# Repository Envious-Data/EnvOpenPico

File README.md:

# EnvOpenPico
A RP2040 Based family of MCU boards

### Intentions and Info
The intentions of this project were mainly to learn about MCU design and also to make a rpi pico like device using a RP2040 that has some improvements or changes that you'd find useful, so far Ive changed the type-c port and added a reset button as well as replaced the buck boost IC with a linear regulator which doesnt generate the same switching noise which makes it good for audio.

Ive retained the USB TP pads and also TP6 which is bootsel in their original positions.
a couple of the GPIOs cant retain their original function since Im not using a RT6150B-33GQW so GPIO23 has an optional mosfet for a default on LED instead of controlling the mode for the buck-boost IC.

Ive also got nothing connected on GPIO29 where as the pico has a mosfet to prevent leakage current, im not sure what the use of this GPIO is but if its a wanted feature I can try to add it back.

Update: 09th Aug 2024 - Raspberry pi has released the RP235XA and RP235XB, I have started work on making variants of the main Pico board to fit the RP2350 and RP2354.

### Permissions
You have my permission to fork and learn from this design for your own projects including if you wish to sell those on as a product. 

### Important!!
I have only had the EnvOpenPico made so the other variants like the PicoLipo and the EliteMicro2040 I cant fully confirm if the design works but since its all derived from the main project I should hope it all works as intended.

### Notes
- You should be able to order these and have them entirely assembled by other PCBA suppliers if they have stock of all the parts, ive made sure to label everything in the schematic properly.
- Please ensure you pick a compatible flash chip, you may need to modify the connections to the flash chip, its setup for Winbond W25QxxJVxxx.

### Other
If you want to see pictures of the main PCB you can check out the _photos folder

PCBway kindly sponsored a batch of PCBs which you can see pictures of inside the _photos folder.

http://pcbway.com

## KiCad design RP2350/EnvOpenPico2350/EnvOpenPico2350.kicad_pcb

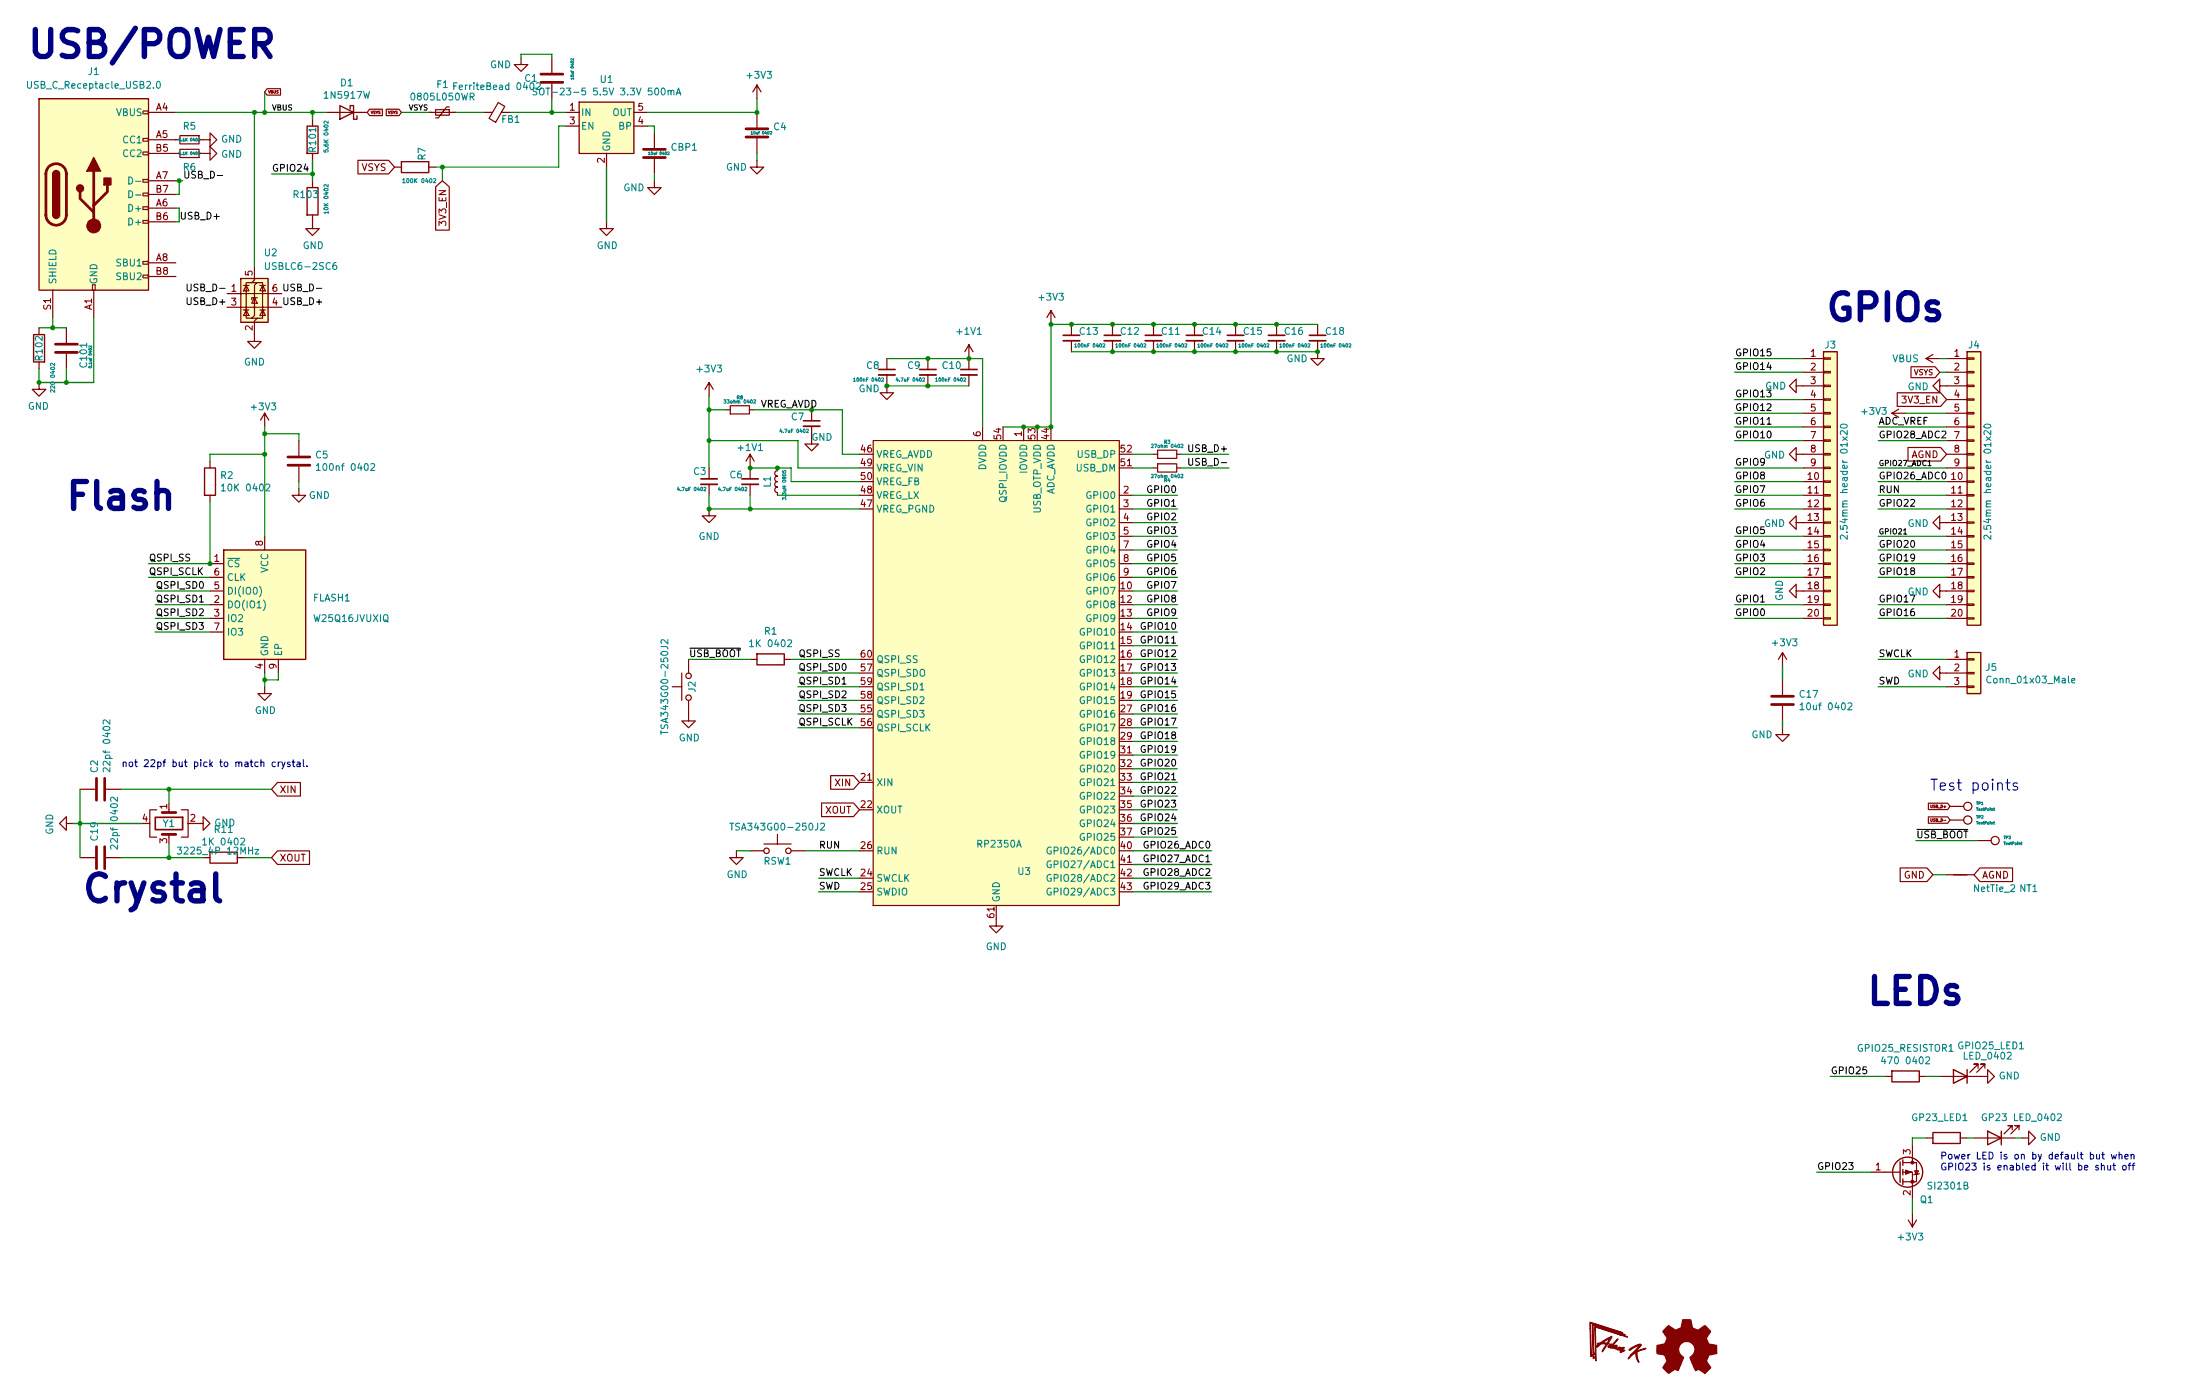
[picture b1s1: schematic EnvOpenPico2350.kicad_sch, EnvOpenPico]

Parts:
C1, C4, C17: 10uf 0402; C_0402_1005Metric
C2, C19: 22pf 0402; C_0402_1005Metric
C3, C6, C7, C9: 4.7uF 0402; C_0402_1005Metric
C5: 100nf 0402; C_0402_1005Metric
C8, C10, C11, C12, C13, C14, C15, C16, C18: 100nF 0402; C_0402_1005Metric
C101: 0.1uf 0402; C_0402_1005Metric
CBP1: 10uf 0402; C_0402_1005Metric
D1: 1N5917W; D_SOD-123
F1: 0805L050WR; Fuse_0805_2012Metric
FB1: FerriteBead 0402; R_0402_1005Metric
FLASH1: W25Q16JVUXIQ; Winbond_USON-8-1EP_3x2mm_P0.5mm_EP0.2x1.6mm
GP23_LED1: GP23 LED_0402; LED_0402_1005Metric
GPIO24_RESISTOR1: 1K 0402; R_0402_1005Metric
GPIO25_LED1: LED_0402; LED_0402_1005Metric
GPIO25_RESISTOR1: 470 0402; R_0402_1005Metric
J1: USB_C_Receptacle_USB2.0; USB_C_Receptacle_HRO_TYPE-C-31-M-12
J2: TSA343G00-250J2; SW_Push_SPST_NO_Alps_SKRK
J3, J4: 2.54mm header 01x20; PinHeader_1x20_P2.54mm_Vertical
J5: Conn_01x03_Male; PinHeader_1x03_P2.54mm_Vertical
L1: 3.3uH 0805; L_0805_2012Metric
NT1: NetTie_2; NetTie-2_SMD_Pad0.5mm
Q1: SI2301B; SOT-23
R1, R11: 1K 0402; R_0402_1005Metric
R2, R103: 10K 0402; R_0402_1005Metric
R3, R4: 27ohm 0402; R_0402_1005Metric
R5, R6: 5.1K 0402; R_0402_1005Metric
R7: 100K 0402; R_0402_1005Metric
R8: 33ohm 0402; R_0402_1005Metric
R101: 5.6K 0402; R_0402_1005Metric
R102: 220 0402; R_0402_1005Metric
RSW1: TSA343G00-250J2; SW_Push_SPST_NO_Alps_SKRK
TP1, TP2, TP3: TestPoint; CustomTestPoint
U1: SOT-23-5 5.5V 3.3V 500mA; SOT-23-5
U2: USBLC6-2SC6; SOT-23-6
U3: RP2350A; QFN-60-1EP_7x7mm_P0.4mm_EP3.4x3.4mm_ThermalVias
Y1: 3225_4P 12MHz; Crystal_SMD_3225-4Pin_3.2x2.5mm

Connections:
3V3_EN: J4.4, R7.1, U1.3 (EN)
+1V1: C6.1, C8.1, C9.1, C10.1, L1.1, U3.6 (DVDD), U3.23 (DVDD), U3.39 (DVDD), U3.50 (VREG_FB)
+3V3: C3.1, C4.1, C5.1, C11.1, C12.1, C13.1, C14.1, C15.1, C16.1, C17.1, C18.1, FLASH1.8 (VCC), J4.5, Q1.2 (S), R2.1, R8.1, U1.5 (OUT), U3.1 (IOVDD), U3.11 (IOVDD), U3.20 (IOVDD), U3.30 (IOVDD), U3.38 (IOVDD), U3.44 (ADC_AVDD), U3.45 (IOVDD), U3.49 (VREG_VIN), U3.53 (USB_OTP_VDD), U3.54 (QSPI_IOVDD)
/ADC_VREF: J4.6
/GPIO0: J3.20, U3.2 (GPIO0)
/GPIO1: J3.19, U3.3 (GPIO1)
/GPIO2: J3.17, U3.4 (GPIO2)
/GPIO3: J3.16, U3.5 (GPIO3)
/GPIO4: J3.15, U3.7 (GPIO4)
/GPIO5: J3.14, U3.8 (GPIO5)
/GPIO6: J3.12, U3.9 (GPIO6)
/GPIO7: J3.11, U3.10 (GPIO7)
/GPIO8: J3.10, U3.12 (GPIO8)
/GPIO9: J3.9, U3.13 (GPIO9)
/GPIO10: J3.7, U3.14 (GPIO10)
/GPIO11: J3.6, U3.15 (GPIO11)
/GPIO12: J3.5, U3.16 (GPIO12)
/GPIO13: J3.4, U3.17 (GPIO13)
/GPIO14: J3.2, U3.18 (GPIO14)
/GPIO15: J3.1, U3.19 (GPIO15)
/GPIO16: J4.20, U3.27 (GPIO16)
/GPIO17: J4.19, U3.28 (GPIO17)
/GPIO18: J4.17, U3.29 (GPIO18)
/GPIO19: J4.16, U3.31 (GPIO19)
/GPIO20: J4.15, U3.32 (GPIO20)
/GPIO21: J4.14, U3.33 (GPIO21)
/GPIO22: J4.12, U3.34 (GPIO22)
/GPIO23: Q1.1 (G), U3.35 (GPIO23)
/GPIO24: R101.2, R103.1, U3.36 (GPIO24)
/GPIO25: GPIO25_RESISTOR1.2, U3.37 (GPIO25)
/GPIO26_ADC0: J4.10, U3.40 (GPIO26/ADC0)
/GPIO27_ADC1: J4.9, U3.41 (GPIO27/ADC1)
/GPIO28_ADC2: J4.7, U3.42 (GPIO28/ADC2)
/GPIO29_ADC3: U3.43 (GPIO29/ADC3)
/QSPI_SCLK: FLASH1.6 (CLK), U3.56 (QSPI_SCLK)
/QSPI_SD0: FLASH1.5 (DI(IO0)), U3.57 (QSPI_SDO)
/QSPI_SD1: FLASH1.2 (DO(IO1)), U3.59 (QSPI_SD1)
/QSPI_SD2: FLASH1.3 (IO2), U3.58 (QSPI_SD2)
/QSPI_SD3: FLASH1.7 (IO3), U3.55 (QSPI_SD3)
/QSPI_SS: FLASH1.1 (~CS), R1.1, R2.2, U3.60 (QSPI_SS)
/RUN: J4.11, RSW1.2, U3.26 (RUN)
/SWCLK: J5.1, U3.24 (SWCLK)
/SWD: J5.3, U3.25 (SWDIO)
/VREG_AVDD: C7.1, R8.2, U3.46 (VREG_AVDD)
/~USB_BOOT: J2.2, R1.2, TP3.1
AGND: J4.8, NT1.2
GND: C1.2, C2.1, C3.2, C4.2, C5.2, C6.2, C7.2, C8.2, C9.2, C10.2, C11.2, C12.2, C13.2, C14.2, C15.2, C16.2, C17.2, C18.2, C19.1, C101.1, CBP1.2, FLASH1.4 (GND), FLASH1.9 (EP), GP23_LED1.1 (K), GPIO25_LED1.1 (K), J1.A1 (GND), J1.A12 (GND), J1.B1 (GND), J1.B12 (GND), J2.1, J3.3, J3.8, J3.13, J3.18, J4.3, J4.13, J4.18, J5.2, NT1.1, R5.1, R6.1, R102.2, R103.2, RSW1.1, U1.2 (GND), U2.2 (GND), U3.47 (VREG_PGND), U3.61 (GND), Y1.2, Y1.4
unnamed: C19.2, R11.2, Y1.3
unnamed: F1.1, FB1.1
unnamed: GP23_LED1.2 (A), GPIO24_RESISTOR1.1
unnamed: GPIO25_LED1.2 (A), GPIO25_RESISTOR1.1
unnamed: J1.A5 (CC1), R5.2
unnamed: J1.B5 (CC2), R6.2
unnamed: C101.2, J1.S1 (SHIELD), R102.1
unnamed: GPIO24_RESISTOR1.2, Q1.3 (D)
unnamed: CBP1.1, U1.4 (BP)
unnamed: C1.1, FB1.2, U1.1 (IN)
unnamed: R4.1, U3.51 (USB_DM)
unnamed: R3.1, U3.52 (USB_DP)
unnamed: L1.2, U3.48 (VREG_LX)
USB_D+: J1.A6 (D+), J1.B6 (D+), R3.2, TP1.1, U2.3 (I/O2), U2.4 (I/O2)
USB_D-: J1.A7 (D-), J1.B7 (D-), R4.2, TP2.1, U2.1 (I/O1), U2.6 (I/O1)
VBUS: D1.2 (A), J1.A4 (VBUS), J1.A9 (VBUS), J1.B4 (VBUS), J1.B9 (VBUS), J4.1, R101.1, U2.5 (VBUS)
VSYS: D1.1 (K), F1.2, J4.2, R7.2
XIN: C2.2, U3.21 (XIN), Y1.1
XOUT: R11.1, U3.22 (XOUT)

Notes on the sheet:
Power LED is on by default but when GPIO23 is enabled it will be shut off
GPIOs
USB/POWER
Flash
not 22pf but pick to match crystal.
Test points
LEDs
Crystal

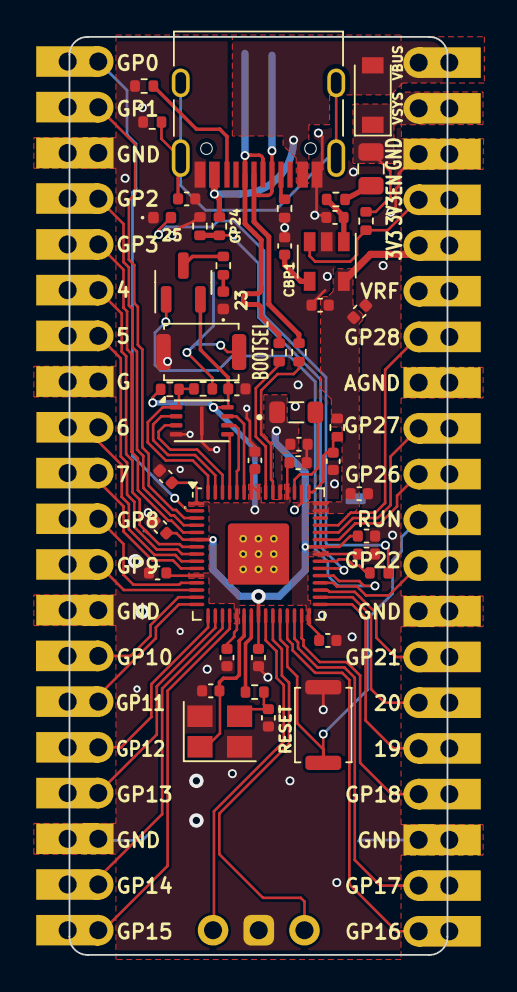
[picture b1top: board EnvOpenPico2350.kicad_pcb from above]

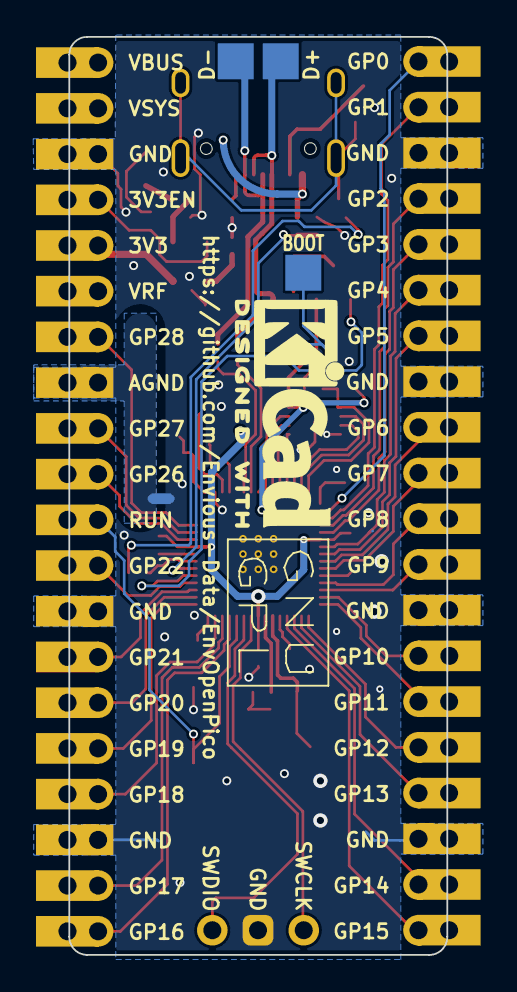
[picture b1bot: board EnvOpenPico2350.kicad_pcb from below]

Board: 2 copper layers, 21.0 x 51.0 mm, 56 parts (6 on the bottom side), 64 nets.

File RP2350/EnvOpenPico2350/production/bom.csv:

Designator,Footprint,Quantity,Value,LCSC Part #
"C1, C17, C4, CBP1",0402,4,10uf 0402, 
"C10, C11, C12, C13, C14, C15, C16, C18, C8",0402,9,100nF 0402,
C101,0402,1,0.1uf 0402, 
"C19, C2",0402,2,22pf 0402, 
"C3, C6, C7, C9",0402,4,4.7uF 0402,
C5,0402,1,100nf 0402, 
D1,D_SOD-123,1,1N5917W, 
F1,0805,1,0805L050WR,
FB1,0402,1,FerriteBead 0402,
FLASH1,Winbond_USON-8-1EP_3x2mm_P0.5mm_EP0.2x1.6mm,1,W25Q16JVUXIQ,
GP23_LED1,0402,1,GP23 LED_0402, 
"GPIO24_RESISTOR1, R1, R11",0402,3,1K 0402, 
GPIO25_LED1,0402,1,LED_0402, 
GPIO25_RESISTOR1,0402,1,470 0402, 
J1,USB_C_Receptacle_HRO_TYPE-C-31-M-12,1,USB_C_Receptacle_USB2.0,
J2,SW_Push_SPST_NO_Alps_SKRK,1,TSA343G00-250J2, 
"J3, J4",PinHeader_1x20_P2.54mm_Vertical,2,2.54mm header 01x20, 
J5,PinHeader_1x03_P2.54mm_Vertical,1,Conn_01x03_Male, 
L1,0805,1,3.3uH 0805,
NT1,NetTie-2_SMD_Pad0.5mm,1,NetTie_2,
Q1,SOT-23,1,SI2301B,
R101,0402,1,5.6K 0402, 
R102,0402,1,220 0402, 
R103,0402,1,10K 0402, 
R2,0402,1,10K 0402,  
"R3, R4",0402,2,27ohm 0402,
"R5, R6",0402,2,5.1K 0402, 
R7,0402,1,100K 0402, 
R8,0402,1,33ohm 0402,
RSW1,SW_Push_SPST_NO_Alps_SKRK,1,TSA343G00-250J2,
"TP1, TP2, TP3",CustomTestPoint,3,TestPoint, 
U1,SOT-23-5,1,SOT-23-5 5.5V 3.3V 500mA, 
U3,QFN-60-1EP_7x7mm_P0.4mm_EP3.4x3.4mm_ThermalVias,1,RP2350A,
Y1,Crystal_SMD_3225-4Pin_3.2x2.5mm,1,3225_4P 12MHz,

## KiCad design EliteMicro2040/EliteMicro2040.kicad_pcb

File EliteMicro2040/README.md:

# EnvOpenPico
A Raspberry Pi RP2040 based board in the shape of an Elite-C.

### Info
This board is about 2.5mm shorter than an Elite-C and uses a mid-mount USB C port.

### some notes
I dont update the readme very often so some info here may end up outdated at some point.

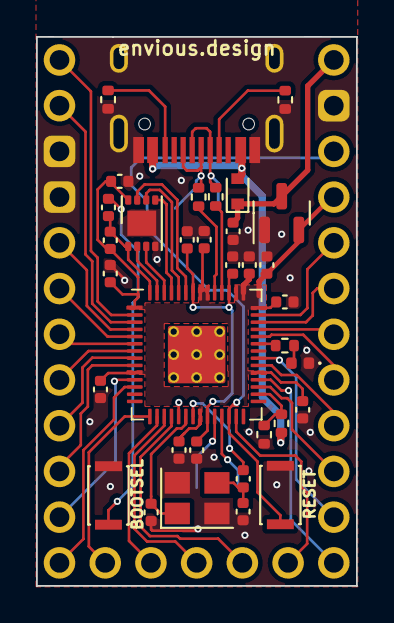
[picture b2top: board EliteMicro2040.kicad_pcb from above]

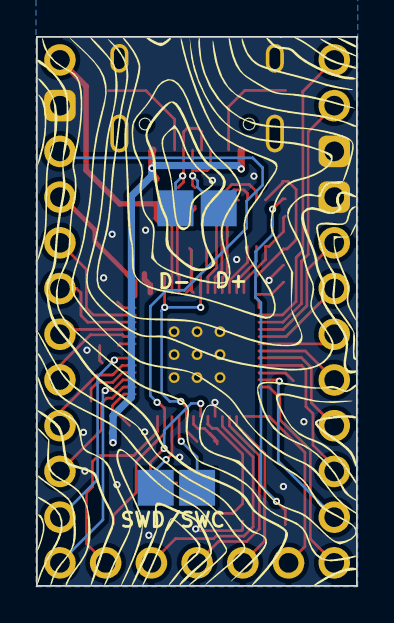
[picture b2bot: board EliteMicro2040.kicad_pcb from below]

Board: 2 copper layers, 17.8 x 30.5 mm, 39 parts (4 on the bottom side), 50 nets.

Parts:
C1, C3, C4, C10: 1uf 0201; C_0402_1005Metric
C2: 22pF 0402; C_0402_1005Metric
C5, C6, C7, C8, C11, C13, C14, C15, C18: 100nf 0201; C_0402_1005Metric
C19: 22pf 0402; C_0402_1005Metric
D1: SOD-523 General; D_SOD-523
FLASH1: W25Q16JVUXIQ; SON-8-1EP_3x2mm_P0.5mm_EP1.4x1.6mm
GPIO25_LED1: LED 0201; LED_0402_1005Metric
GPIO25_RESISTOR1: 1K 0201; R_0402_1005Metric
J1, J2: Button; SW_SPST_CK_KXT3
R1, R7: 1K 0201; C_0402_1005Metric
R2: 10K 0201; C_0402_1005Metric
R3, R4: 27r 0201; R_0402_1005Metric
R5, R6: 5.1K 0201; R_0402_1005Metric
R101: 5.6k 0201; R_0402_1005Metric
R102: 10k 0201; R_0402_1005Metric
TP1, TP2, TP101, TP103: TestPoint; CustomTestPoint
U1: ZL6201A33S3; SOT-23
U2: Elite-C
U3: RP2040; RP2040-QFN-56
USB2: HRO-TYPE-C-31-M-12
Y1: 3225-4P 12MHz; Crystal_SMD_3225-4Pin_3.2x2.5mm

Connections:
+1V1: C3.1, C6.1, C7.1, U3.23 (DVDD), U3.45 (VREG_VOUT), U3.50 (DVDD)
+3V3: C4.1, C5.1, C8.1, C10.1, C11.1, C13.1, C14.1, C15.1, C18.1, FLASH1.8 (VCC), R2.1, U1.2 (VO), U2.21 (VCC), U3.1 (IOVDD), U3.10 (IOVDD), U3.22 (IOVDD), U3.33 (IOVDD), U3.42 (IOVDD), U3.43 (ADC_AVDD), U3.44 (VREG_IN), U3.48 (USB_VDD), U3.49 (IOVDD)
/GPIO0: U2.1 (TX0/PD3), U3.2 (GPIO0)
/GPIO1: U2.2 (RX1/PD2), U3.3 (GPIO1)
/GPIO2: U2.5 (2/PD1), U3.4 (GPIO2)
/GPIO3: U2.6 (3/PD0), U3.5 (GPIO3)
/GPIO4: U2.7 (4/PD4), U3.6 (GPIO4)
/GPIO5: U2.8 (5/PC6), U3.7 (GPIO5)
/GPIO6: U2.9 (6/PD7), U3.8 (GPIO6)
/GPIO7: U2.10 (7/PE6), U3.9 (GPIO7)
/GPIO8: U2.11 (8/PB4), U3.11 (GPIO8)
/GPIO9: U2.12 (9/PB5), U3.12 (GPIO9)
/GPIO12: U2.25 (B7), U3.15 (GPIO12)
/GPIO13: U2.26 (D5), U3.16 (GPIO13)
/GPIO14: U2.27 (C7), U3.17 (GPIO14)
/GPIO15: U2.28 (F1), U3.18 (GPIO15)
/GPIO16: U2.29 (F0), U3.27 (GPIO16)
/GPIO19: R101.2, R102.1, U3.30 (GPIO19)
/GPIO20: U2.15 (14/PB3), U3.31 (GPIO20)
/GPIO21: U2.13 (10/PB6), U3.32 (GPIO21)
/GPIO22: U2.16 (15/PB1), U3.34 (GPIO22)
/GPIO23: U2.14 (16/PB2), U3.35 (GPIO23)
/GPIO25: GPIO25_RESISTOR1.2, U3.37 (GPIO25)
/GPIO26_ADC0: U2.17 (A0/PF7), U3.38 (GPIO26_ADC0)
/GPIO27_ADC1: U2.18 (A1/PF6), U3.39 (GPIO27_ADC1)
/GPIO28_ADC2: U2.19 (A2/PF5), U3.40 (GPIO28_ADC2)
/GPIO29_ADC3: U2.20 (A3/PF4), U3.41 (GPIO29_ADC3)
/QSPI_SCLK: FLASH1.6 (CLK), U3.52 (QSPI_SCLK)
/QSPI_SD0: FLASH1.5 (DI(IO0)), U3.53 (QSPI_SD0)
/QSPI_SD1: FLASH1.2 (DO(IO1)), U3.55 (QSPI_SD1)
/QSPI_SD2: FLASH1.3 (IO2), U3.54 (QSPI_SD2)
/QSPI_SD3: FLASH1.7 (IO3), U3.51 (QSPI_SD3)
/QSPI_SS: FLASH1.1 (~CS), R1.1, R2.2, U3.56 (QSPI_SS)
/RUN: J1.1, U2.22 (RST), U3.26 (RUN)
/SWCLK: TP101.1, U3.24 (SWCLK)
/SWD: TP103.1, U3.25 (SWD)
/~USB_BOOT: J2.1, R1.2
GND: C1.2, C2.2, C3.2, C4.2, C5.2, C6.2, C7.2, C8.2, C10.2, C11.2, C13.2, C14.2, C15.2, C18.2, C19.2, FLASH1.4 (GND), FLASH1.9 (EP), GPIO25_LED1.1 (K), J1.2, J2.2, R5.1, R6.1, R102.2, U1.1 (GND), U2.3 (GND), U2.4 (GND), U2.23 (GND), U3.19 (TESTEN), U3.57 (GND), USB2.1 (GND), USB2.12 (GND), USB2.13 (SHIELD), Y1.2, Y1.4
unnamed: C2.1, R7.1, Y1.3
unnamed: GPIO25_LED1.2 (A), GPIO25_RESISTOR1.1
unnamed: R4.2, U3.46 (USB_DM)
unnamed: R3.2, U3.47 (USB_DP)
unnamed: C19.1, U3.20 (XIN), Y1.1
unnamed: R7.2, U3.21 (XOUT)
unnamed: R5.2, USB2.4 (CC1)
unnamed: R6.2, USB2.10 (CC2)
USB_D+: R3.1, TP1.1, USB2.6 (DP1), USB2.8 (DP2)
USB_D-: R4.1, TP2.1, USB2.5 (DN2), USB2.7 (DN1)
VBUS: D1.2 (A), R101.1, USB2.2 (VBUS), USB2.11 (VBUS)
VSYS: C1.1, D1.1 (K), U1.3 (VI), U2.24 (B0)

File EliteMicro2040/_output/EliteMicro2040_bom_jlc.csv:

"Comment","Designator","Footprint","LCSC Part #"
"1uf 0201","C1,C3,C4,C10","C_0201_0603Metric","no_part_number"
"22pF 0402","C2","C_0402_1005Metric","no_part_number"
"100nf 0201","C5,C6,C7,C8,C11,C13,C14,C15,C16,C18","C_0201_0603Metric","no_part_number"
"22pf 0402","C19","C_0402_1005Metric","no_part_number"
"SOD-523 General","D1","D_SOD-523","no_part_number"
"W25Q16JVUXIQ","FLASH1","SON-8-1EP_3x2mm_P0.5mm_EP1.4x1.6mm","no_part_number"
"LED 0201","GPIO25_LED1","LED_0201_0603Metric","no_part_number"
"1K 0201","GPIO25_RESISTOR1","R_0201_0603Metric","no_part_number"
"Button","J1,J2","SW_SPST_CK_KXT3","no_part_number"
"1K 0201","R1,R7","C_0201_0603Metric","no_part_number"
"10K 0201","R2","C_0201_0603Metric","no_part_number"
"27r 0201","R3,R4","R_0201_0603Metric","no_part_number"
"5.1K 0201","R5,R6","R_0201_0603Metric","no_part_number"
"5.6k 0201","R101","R_0201_0603Metric","no_part_number"
"10k 0201","R102","R_0201_0603Metric","no_part_number"
"TestPoint","TP1,TP2,TP101,TP103","CustomTestPoint","no_part_number"
"ZL6201A33S3","U1","SOT-23","no_part_number"
"Elite-C","U2","Elite-C","no_part_number"
"RP2040","U3","RP2040-QFN-56","C2040"
"TYPE-C-31-M-14","USB1","USB_C_TYPE-C-31-M-14","C223907"
"3225-4P 12MHz","Y1","Crystal_SMD_3225-4Pin_3.2x2.5mm","no_part_number"

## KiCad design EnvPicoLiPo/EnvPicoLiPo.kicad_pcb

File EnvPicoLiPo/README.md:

# EnvOpenPico
A Raspberry Pi Pico Clone which also uses the RP2040.

## THIS PROJECT IS FOR KICAD 5.99
because there are a couple features of kicad 5.99 that I need this project will be done in kicad 5.99 instead of kicad stable.

### Info
This version of the board uses a PMIC namely BQ24072RGT this is paired with a LM3671MF 3.3V to get the rpi pico its 3.3V, there is also a ESP32-PICO-D4 for wifi and bluetooth and maybe later it can be used as an IO expander.

### problems
I must point out that alike most things on my github im learning as I go so some pointers on doing things correctly would be apreciated.

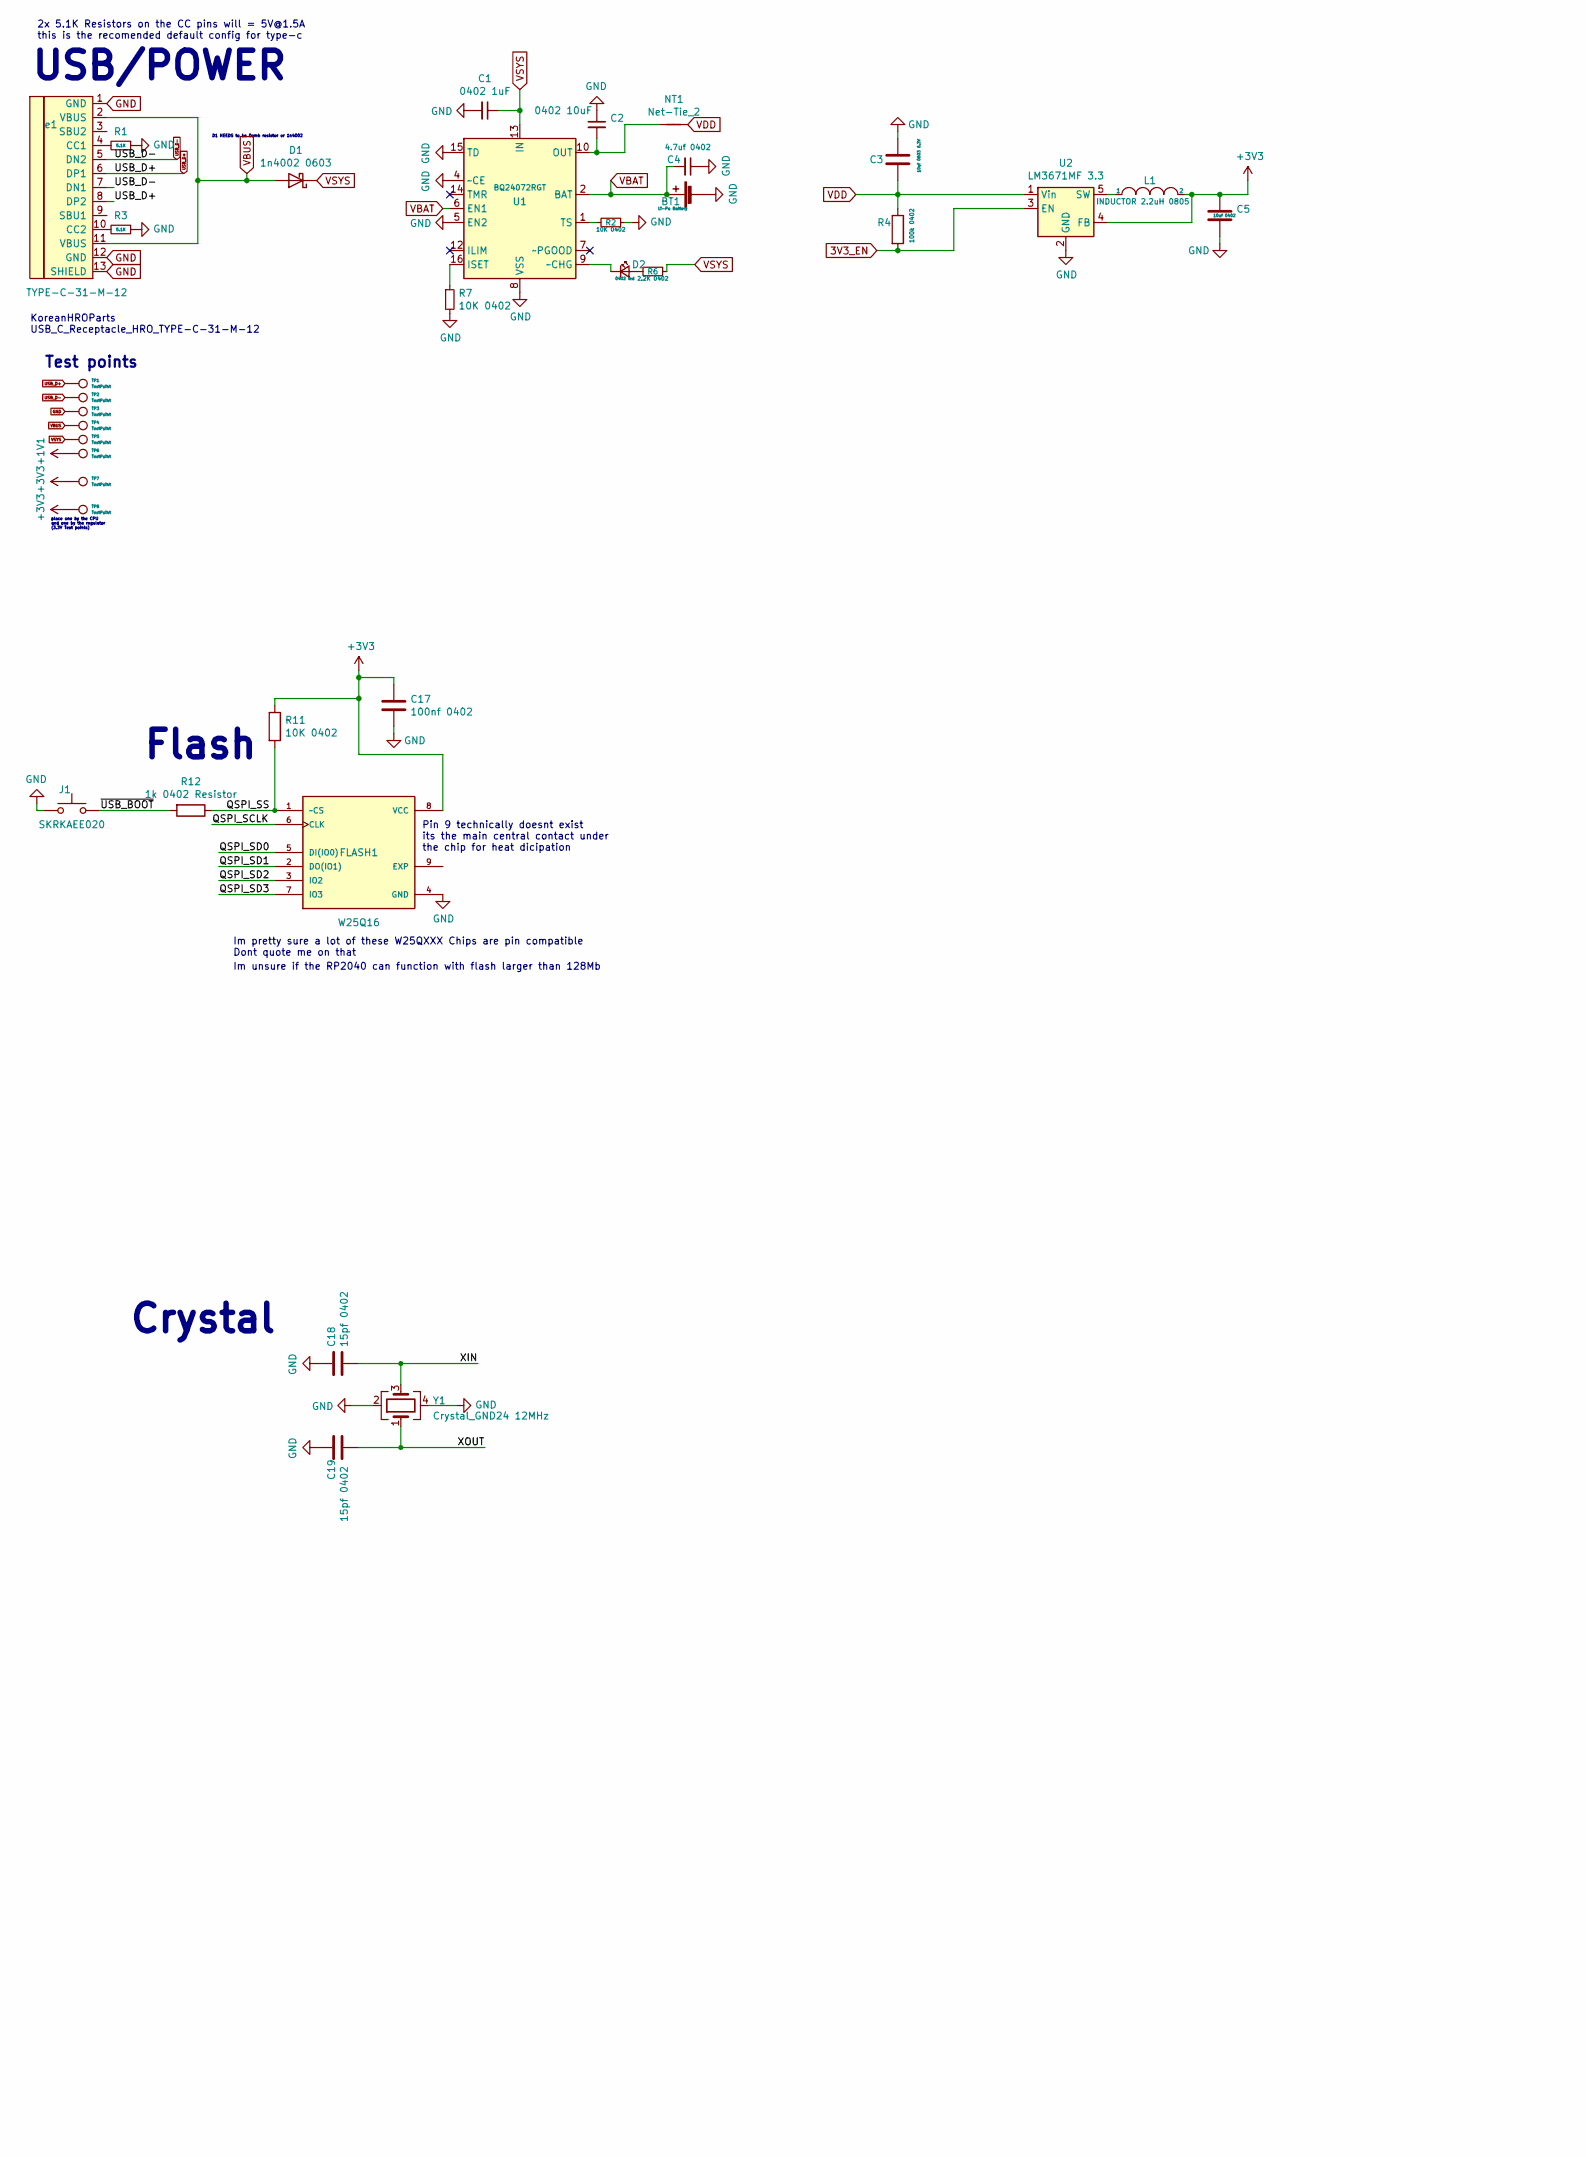
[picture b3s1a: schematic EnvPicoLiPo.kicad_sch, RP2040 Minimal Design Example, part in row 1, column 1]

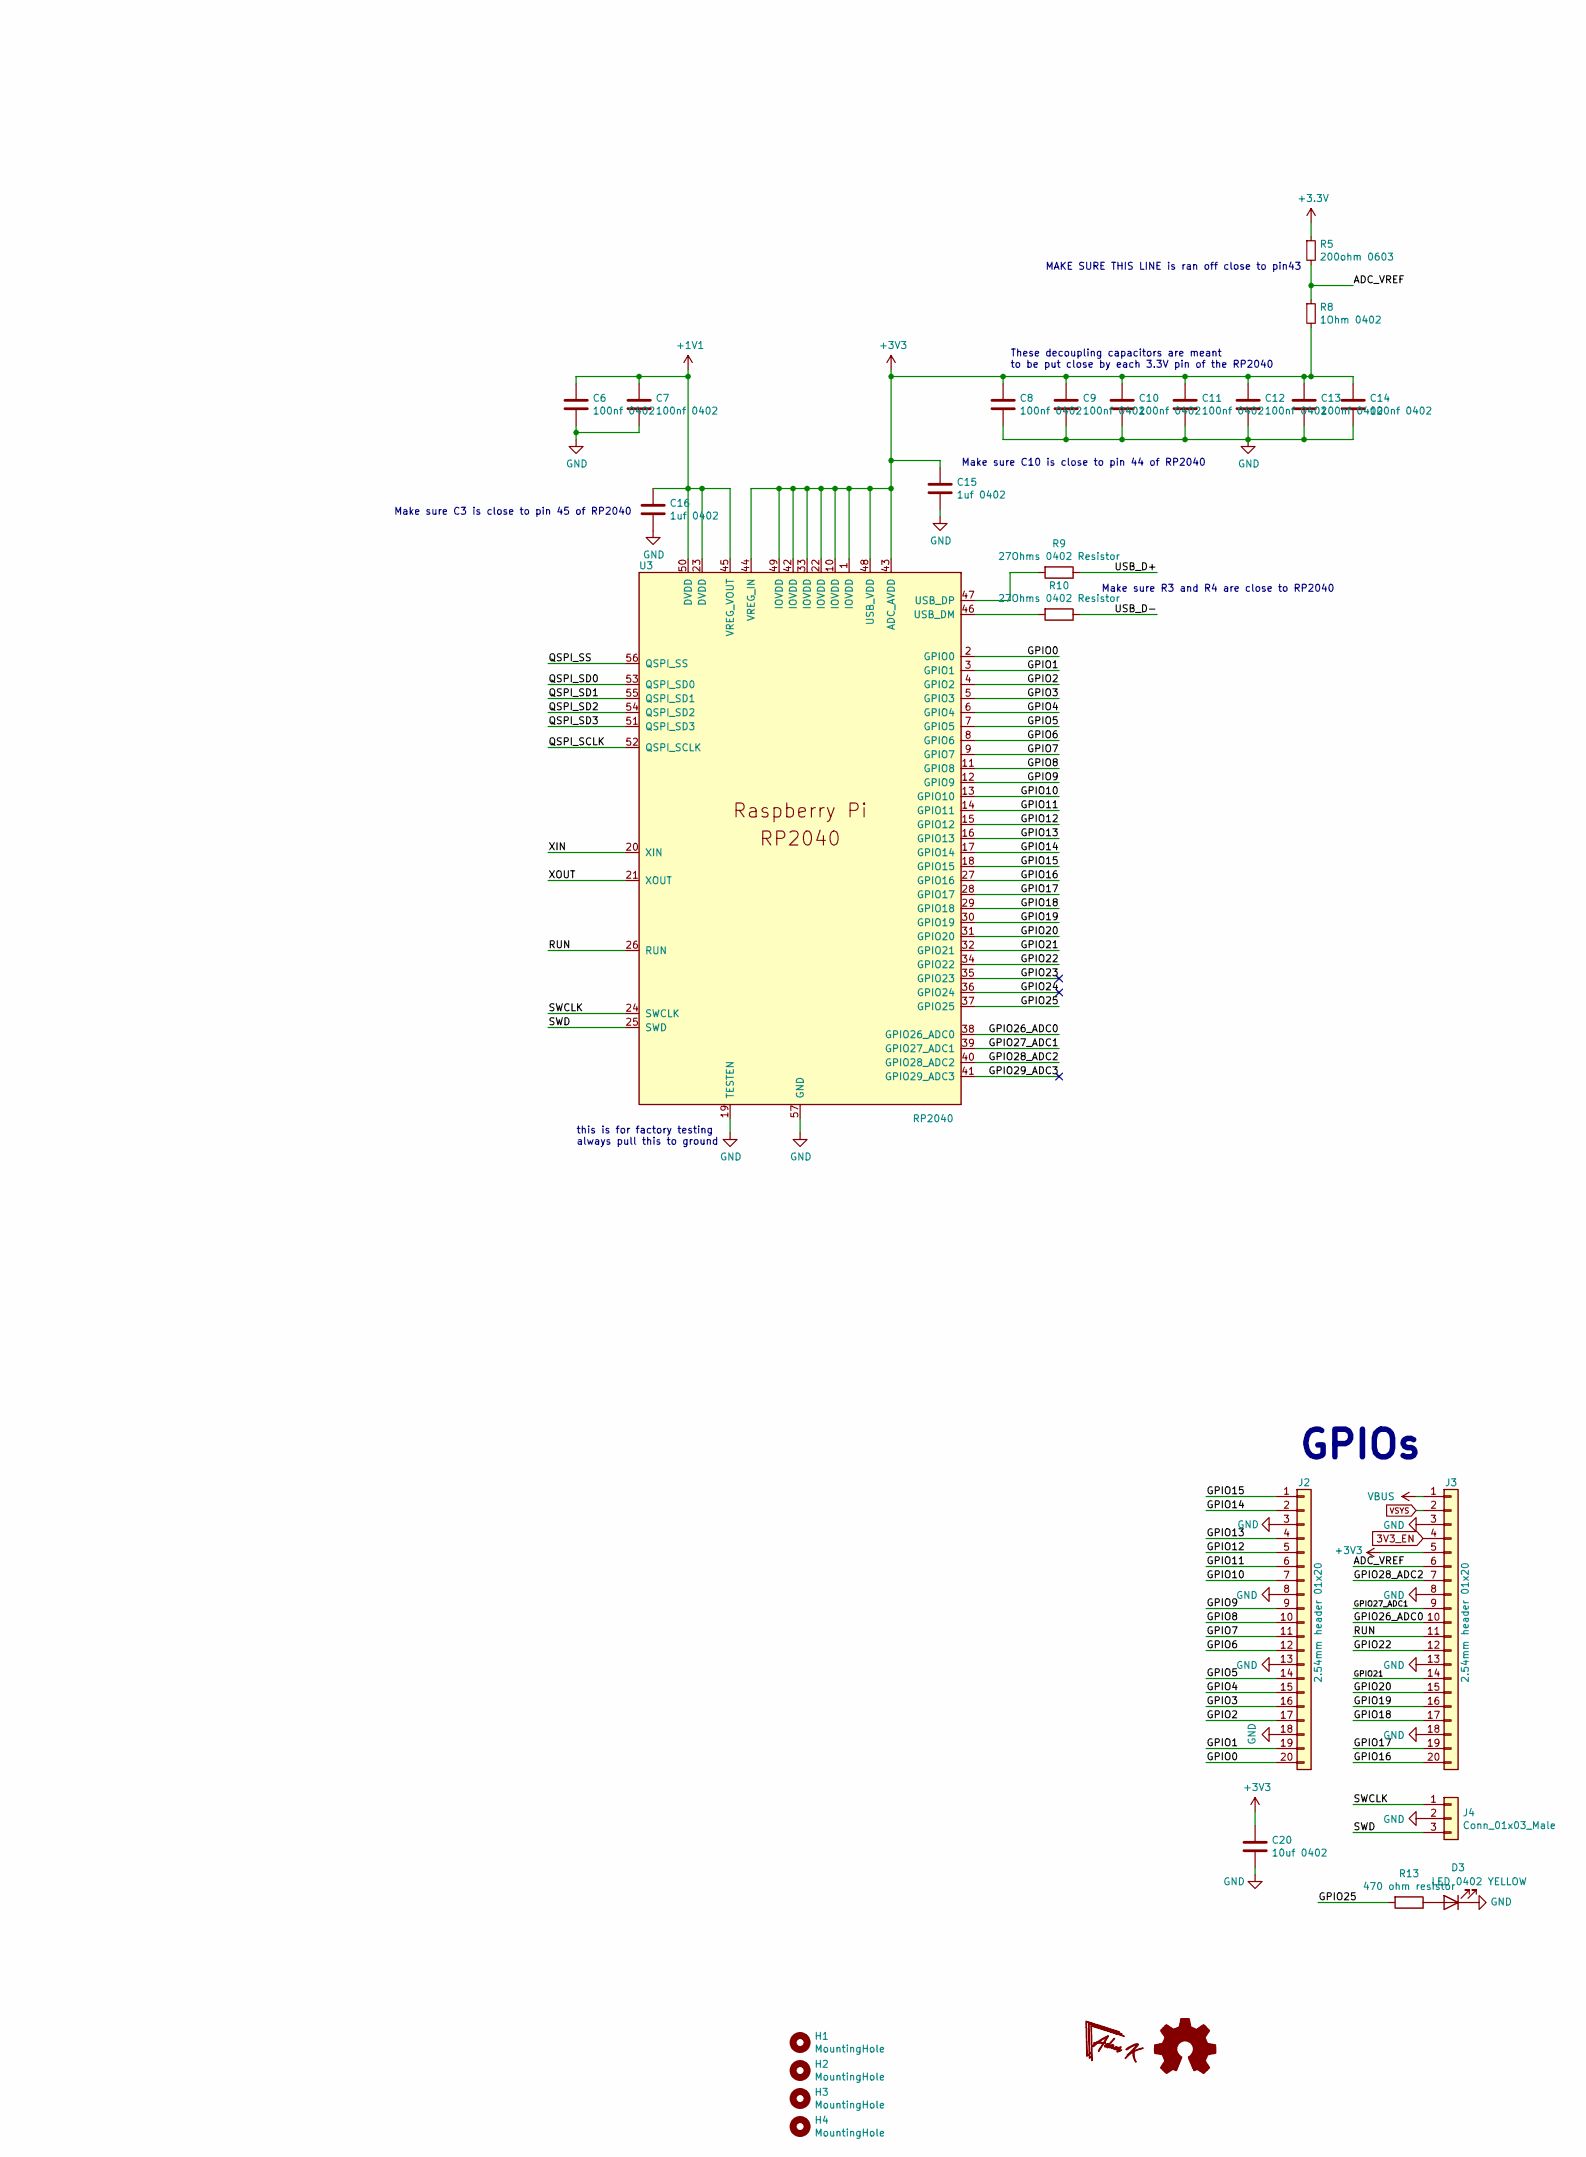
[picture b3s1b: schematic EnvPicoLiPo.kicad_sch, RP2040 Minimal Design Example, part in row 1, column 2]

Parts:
BT1: Li-Po Battery; JST_XH_B2B-XH-A_1x02_P2.50mm_Vertical
C1: 0402 1uF; C_0402_1005Metric
C2: 0402 10uF; R_0402_1005Metric
C3: 10uf 0603 6.3V; C_0603_1608Metric
C4: 4.7uf 0402; C_0402_1005Metric
C5, C20: 10uf 0402; C_0402_1005Metric
C6, C7, C8, C9, C10, C11, C12, C13, C14, C17: 100nf 0402; C_0402_1005Metric
C15, C16: 1uf 0402; C_0402_1005Metric
C18, C19: 15pf 0402; C_0402_1005Metric
D1: 1n4002 0603; D_0603_1608Metric
D2: 0402 led; LED_0402_1005Metric
D3: LED 0402 YELLOW; LED_0402_1005Metric
FLASH1: W25Q16; SON-8-1EP_3x2mm_P0.5mm_EP1.4x1.6mm
H1, H2, H3, H4: MountingHole; MountingHole_2.2mm_M2
J1: SKRKAEE020; SW_Push_SPST_NO_Alps_SKRK
J2, J3: 2.54mm header 01x20; PinHeader_1x20_P2.54mm_Vertical
J4: Conn_01x03_Male; PinHeader_1x03_P2.54mm_Vertical
L1: INDUCTOR 2.2uH 0805; L_0805_2012Metric
NT1: Net-Tie_2; NetTie-2_SMD_Pad0.5mm
R1, R3: 5.1K; R_0402_1005Metric
R2, R7: 10K 0402; R_0402_1005Metric
R4: 100k 0402; R_0402_1005Metric
R5: 200ohm 0603; R_0603_1608Metric
R6: 2.2K 0402; R_0402_1005Metric
R8: 1Ohm 0402; R_0402_1005Metric
R9, R10: 27Ohms 0402 Resistor; C_0402_1005Metric
R11: 10K 0402; C_0402_1005Metric
R12: 1k 0402 Resistor; C_0402_1005Metric
R13: 470 ohm resistor; R_0402_1005Metric
TP1, TP2, TP3, TP4, TP5, TP6, TP7, TP8: TestPoint; TestPoint_Pad_D1.0mm
U1: BQ24072RGT; VQFN-16-1EP_3x3mm_P0.5mm_EP1.6x1.6mm
U2: LM3671MF 3.3; TSOT-23-5
U3: RP2040; RP2040-QFN-56
Y1: Crystal_GND24 12MHz; Crystal_SMD_3225-4Pin_3.2x2.5mm
e1: TYPE-C-31-M-12; HRO-TYPE-C-31-M-12

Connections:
3V3_EN: J3.4, R4.2, U2.3 (EN)
+1V1: C6.1, C7.1, C16.1, TP6.1, U3.23 (DVDD), U3.45 (VREG_VOUT), U3.50 (DVDD)
/ADC_VREF: J3.6, R5.2, R8.1
/GPIO0: J2.20, U3.2 (GPIO0)
/GPIO1: J2.19, U3.3 (GPIO1)
/GPIO2: J2.17, U3.4 (GPIO2)
/GPIO3: J2.16, U3.5 (GPIO3)
/GPIO4: J2.15, U3.6 (GPIO4)
/GPIO5: J2.14, U3.7 (GPIO5)
/GPIO6: J2.12, U3.8 (GPIO6)
/GPIO7: J2.11, U3.9 (GPIO7)
/GPIO8: J2.10, U3.11 (GPIO8)
/GPIO9: J2.9, U3.12 (GPIO9)
/GPIO10: J2.7, U3.13 (GPIO10)
/GPIO11: J2.6, U3.14 (GPIO11)
/GPIO12: J2.5, U3.15 (GPIO12)
/GPIO13: J2.4, U3.16 (GPIO13)
/GPIO14: J2.2, U3.17 (GPIO14)
/GPIO15: J2.1, U3.18 (GPIO15)
/GPIO16: J3.20, U3.27 (GPIO16)
/GPIO17: J3.19, U3.28 (GPIO17)
/GPIO18: J3.17, U3.29 (GPIO18)
/GPIO19: J3.16, U3.30 (GPIO19)
/GPIO20: J3.15, U3.31 (GPIO20)
/GPIO21: J3.14, U3.32 (GPIO21)
/GPIO22: J3.12, U3.34 (GPIO22)
/GPIO23: U3.35 (GPIO23)
/GPIO24: U3.36 (GPIO24)
/GPIO25: R13.2, U3.37 (GPIO25)
/GPIO26_ADC0: J3.10, U3.38 (GPIO26_ADC0)
/GPIO27_ADC1: J3.9, U3.39 (GPIO27_ADC1)
/GPIO28_ADC2: J3.7, U3.40 (GPIO28_ADC2)
/GPIO29_ADC3: U3.41 (GPIO29_ADC3)
/QSPI_SCLK: FLASH1.6 (CLK), U3.52 (QSPI_SCLK)
/QSPI_SD0: FLASH1.5 (DI(IO0)), U3.53 (QSPI_SD0)
/QSPI_SD1: FLASH1.2 (DO(IO1)), U3.55 (QSPI_SD1)
/QSPI_SD2: FLASH1.3 (IO2), U3.54 (QSPI_SD2)
/QSPI_SD3: FLASH1.7 (IO3), U3.51 (QSPI_SD3)
/QSPI_SS: FLASH1.1 (~CS), R11.2, R12.1, U3.56 (QSPI_SS)
/RUN: J3.11, U3.26 (RUN); also elsewhere on the board
/SWCLK: J4.1, U3.24 (SWCLK)
/SWD: J4.3, U3.25 (SWD)
/XIN: C18.2, U3.20 (XIN), Y1.3
/~USB_BOOT: J1.1, R12.2
GND: BT1.2 (-), C1.2, C2.1, C3.2, C4.1, C5.2, C6.2, C7.2, C8.2, C9.2, C10.2, C11.2, C12.2, C13.2, C14.2, C15.2, C16.2, C17.2, C18.1, C19.1, C20.2, D3.1 (K), FLASH1.4 (GND), FLASH1.9 (EXP), J1.2, J2.3, J2.8, J2.13, J2.18, J3.3, J3.8, J3.13, J3.18, J4.2, R1.1, R2.1, R3.1, R7.2, TP3.1, U1.4 (~CE), U1.5 (EN2), U1.8 (VSS), U1.15 (TD), U1.17 (VSS), U2.2 (GND), U3.19 (TESTEN), U3.57 (GND), Y1.2, Y1.4, e1.1 (GND), e1.12 (GND), e1.13 (SHIELD); also elsewhere on the board
unnamed: C2.2, NT1.1, U1.10 (OUT), U1.11 (OUT)
unnamed: D2.2 (A), R6.2
unnamed: D2.1 (K), U1.9 (~CHG)
unnamed: D3.2 (A), R13.1
unnamed: R7.1, U1.16 (ISET)
unnamed: R2.2, U1.1 (TS)
unnamed: L1.1, U2.5 (SW)
unnamed: R10.2, U3.46 (USB_DM)
unnamed: R9.2, U3.47 (USB_DP)
unnamed: R1.2, e1.4 (CC1)
unnamed: R3.2, e1.10 (CC2)
USB_D+: R9.1, TP1.1, e1.6 (DP1), e1.8 (DP2)
USB_D-: R10.1, TP2.1, e1.5 (DN2), e1.7 (DN1)
VBAT: BT1.1 (+), C4.2, U1.2 (BAT), U1.3 (BAT), U1.6 (EN1)
VBUS: D1.2 (A), J3.1, TP4.1, e1.2 (VBUS), e1.11 (VBUS)
VDD: C3.1, NT1.2, R4.1, U2.1 (Vin)
VSYS: C1.1, D1.1 (K), J3.2, R6.1, TP5.1, U1.13 (IN)

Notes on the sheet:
USB/POWER
KoreanHROParts USB_C_Receptacle_HRO_TYPE-C-31-M-12
2x 5.1K Resistors on the CC pins will = 5V@1.5A this is the recomended default config for type-c
Test points
place one by the CPU and one by the regulator (3.3V Test points)
Crystal
Flash
D1 NEEDS to be 0omh resistor or 1n4002
Im pretty sure a lot of these W25QXXX Chips are pin compatible Dont quote me on that
Im unsure if the RP2040 can function with flash larger than 128Mb
Pin 9 technically doesnt exist its the main central contact under the chip for heat dicipation
this is for factory testing always pull this to ground
Make sure C3 is close to pin 45 of RP2040
Make sure C10 is close to pin 44 of RP2040
These decoupling capacitors are meant to be put close by each 3.3V pin of the RP2040
MAKE SURE THIS LINE is ran off close to pin43
Make sure R3 and R4 are close to RP2040
GPIOs

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
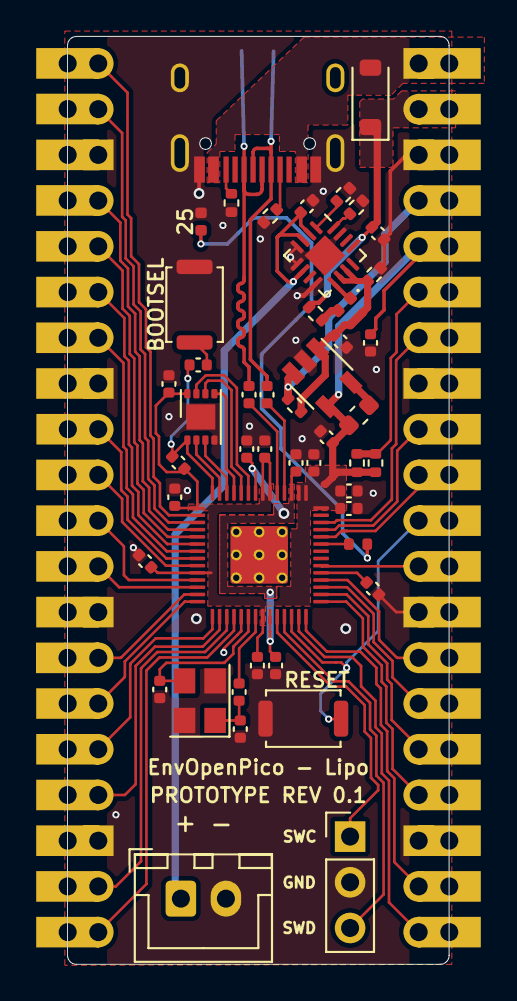
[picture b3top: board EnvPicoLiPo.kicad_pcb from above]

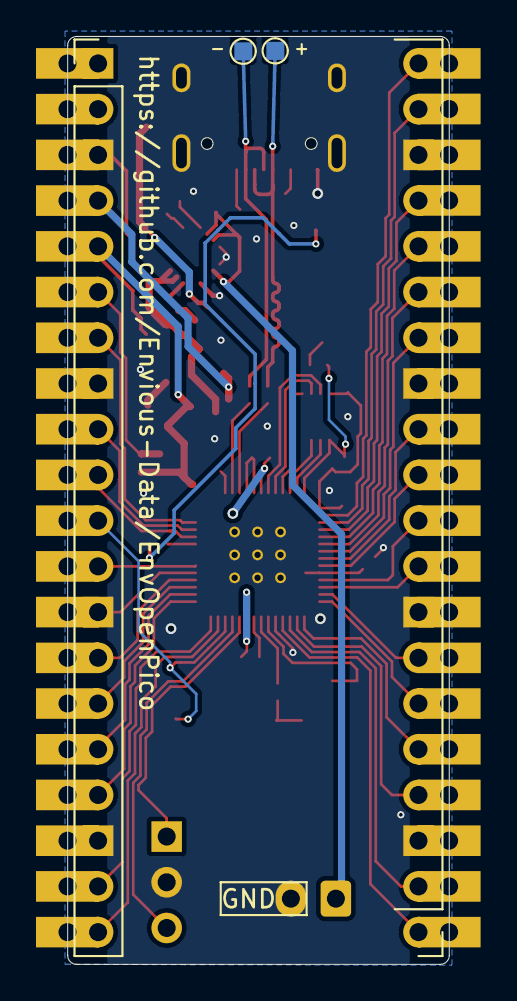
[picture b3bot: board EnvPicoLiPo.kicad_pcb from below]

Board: 2 copper layers, 21.2 x 51.6 mm, 57 parts (4 on the bottom side), 62 nets.

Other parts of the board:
J5: SKRKAEE020; SW_Push_SPST_NO_Alps_SKRK
R14: 1K 0402; C_0402_1005Metric

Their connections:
/RUN: J5.1; also elsewhere on the board
GND: J5.2; also elsewhere on the board
